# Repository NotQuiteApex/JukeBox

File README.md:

# 

An affordable, adorable, powerful hotkey device to run macros, play funny sounds, mute your microphone, change paint brush settings, or manage items in OBS! It can even have RGB or show PC stats!

(TODO: image here)

# Disclaimer
While this project is public, it is not ready for any sort of prime time.

# Docs and Assets
If you are the proud owner of a new JukeBox, or are building your own, take a look at the [getting started doc](docs/getting-started.md).

Sadly, not every program is compatible with these additional function keys, and some do not allow the use of these keys. There is a running list [here](docs/program-compatibility.md) of what programs do and do not work with the keys provided by JukeBox.

# Nightly builds
Each component of the project is built as it is updated. You can grab the latest version of each below. Nightly links provided by [nightly.link](https://nightly.link/).

| [Software, Windows (N/A)](https://nightly.link/FriendTeamInc/JukeBox/workflows/build-software.yaml/main/jb-software-windows.zip) | [Software, Linux](https://nightly.link/FriendTeamInc/JukeBox/workflows/build-software.yaml/main/jb-software-linux.zip) | [Firmware](https://nightly.link/FriendTeamInc/JukeBox/workflows/build-firmware.yaml/main/jb-firmware.zip) | [Hardware, Case](https://nightly.link/FriendTeamInc/JukeBox/workflows/build-hardware-case.yaml/main/jb-hardware-case.zip) | [Hardware, PCB](https://nightly.link/FriendTeamInc/JukeBox/workflows/build-hardware-pcb.yaml/main/jb-hardware-pcb.zip) |
| - | - | - | - | - |

# License
Copyright (c) 2020-2025 Logan "NotQuiteApex" Hickok-Dickson

All programming files, found in [`firmware/`](firmware/), [`software/`](software/), and [`hardware-case/`](hardware-case), are licensed under the [MIT license](https://mit-license.org/). All CAD files, found in [`hardware-pcb/`](hardware-pcb/), unless otherwise provided by an external source such as footprints or 3D models, are licesned under the [CC BY-NC-SA license](https://creativecommons.org/licenses/by-nc-sa/4.0/). Both licenses can be found with the given links or as files in the root of this repostiory.

If you would like to sell a variation of the board designed by you, reach out and an alternative license can be discussed and granted.

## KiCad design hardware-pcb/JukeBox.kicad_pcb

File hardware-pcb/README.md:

# JukeBox PCB
Made with KiCad 8, the PCB is the physical heart of the project.

Footprints and models:
- [Cherry/Kailh Switch footprint based on this.](https://github.com/luke-schutt/Pi5Keyboard/blob/main/Pi5-pcb/Pi5Footprints.pretty/Low%20Profile%20GC%20plus%20MX.kicad_mod)

Estimated power usage is 5 volts at 0.1 amps, or 0.5 watts.

## Bill of Materials
| Ref         | Part No.           | Qty | Value |
|-------------|--------------------|-----|-------|
| R1, R5, R14 | RMCF0402FT1K00     | 3   | 1k    |
| R3, R4      | RMCF0402FT27R0     | 2   | 27    |
| R6, R7      | RMCF0402FT5K11     | 2   | 5.11k |
| R8-12, R15  | RMCF0402FT10K0     | 5   | 10k   |
| R13         | RMCF0402FT10R0     | 1   | 10    |
| C1, C4      | GRM21BR61C106KE15K | 2   | 10u   |
| C2, C3      | GCM1555C1H150JA16D | 2   | 15p   |
| C5          | GRM155R71E104KE14J | 1   | 100n  |
| C8, C10     | GRM155C81A105KA12D | 2   | 1u    |
| D1-12       | 1N4148W-SOD-123    | 12  |       |
| D13-24      | WS2812B-2020       | 12  |       |
| D25         | 150080GS75000      | 1   |       |
| J1          | USB4105-GF-A       | 1   |       |
| Q1          | S8050-SOT-23       | 1   |       |
| U1          | AZ1117IH-3.3TRG1   | 1   |       |
| U2          | W25Q128JVSIQ-TR    | 1   |       |
| U3          | RP2040             | 1   |       |
| U4          | TFTQ-T20SH12ZP01   | 1   |       |
| U5          | CAT24C512          | 1   |       |
| Y1          | ABM8-272-T3        | 1   |       |

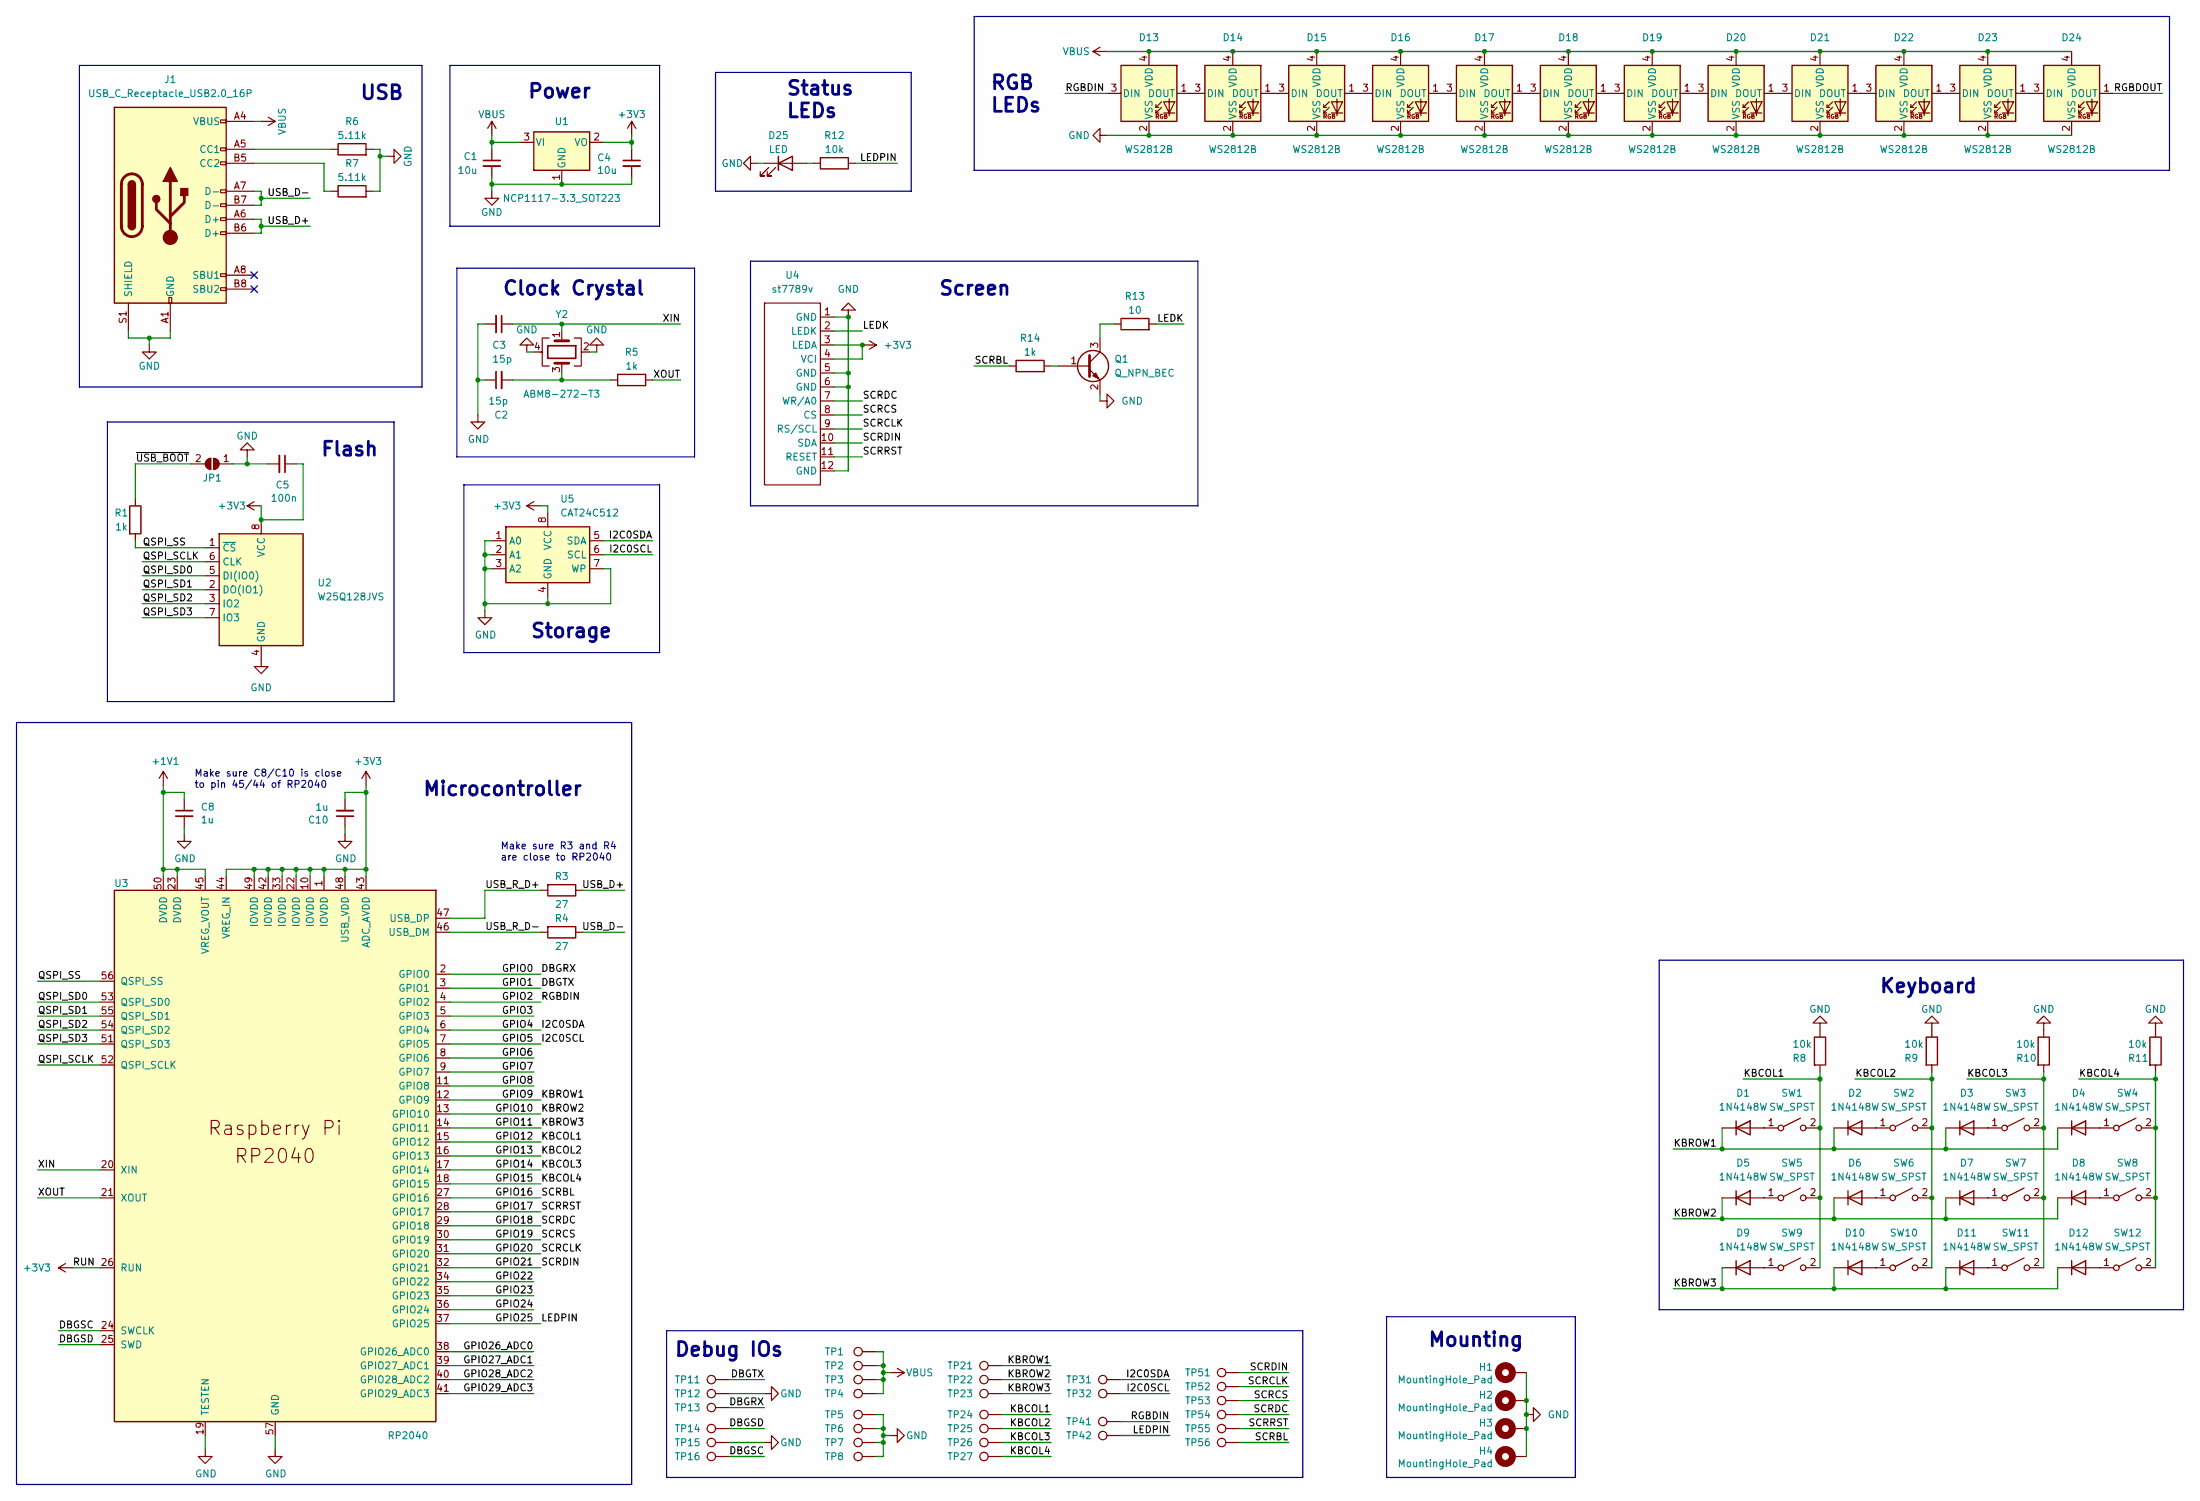
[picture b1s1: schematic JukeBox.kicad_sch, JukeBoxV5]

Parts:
C1, C4: 10u; C_0805_2012Metric
C2, C3: 15p; C_0402_1005Metric
C5: 100n; C_0402_1005Metric
C8, C10: 1u; C_0402_1005Metric
D1, D2, D3, D4, D5, D6, D7, D8, D9, D10, D11, D12: 1N4148W; D_SOD-123
D13, D14, D15, D16, D17, D18, D19, D20, D21, D22, D23, D24: WS2812B; LED_WS2812B-2020_PLCC4_2.0x2.0mm
D25: LED; D_0805_2012Metric_Pad1.15x1.40mm_HandSolder
H1, H2, H3, H4: MountingHole_Pad; MountingHole_3.2mm_M3_Pad_Via
J1: USB_C_Receptacle_USB2.0_16P; USB_C_Receptacle_GCT_USB4105-xx-A_16P_TopMnt_Horizontal
JP1: SolderJumper_2_Open; SolderJumper-2_P1.3mm_Open_RoundedPad1.0x1.5mm
Q1: Q_NPN_BEC; SOT-23
R1, R5, R14: 1k; R_0402_1005Metric
R3, R4: 27; R_0402_1005Metric
R6, R7: 5.11k; R_0402_1005Metric
R8, R9, R10, R11, R12: 10k; R_0402_1005Metric
R13: 10; R_0402_1005Metric
SW1, SW2, SW3, SW4, SW5, SW6, SW7, SW8, SW9, SW10, SW11, SW12: SW_SPST; ALLKEY
TP1, TP2, TP3, TP4, TP5, TP6, TP7, TP8, TP11, TP12, TP13, TP14, TP15, TP16, TP21, TP22, TP23, TP24, TP25, TP26, TP27, TP31, TP32, TP41, TP42, TP51, TP52, TP53, TP54, TP55, TP56: TestPoint; TestPoint_Pad_D1.5mm
U1: NCP1117-3.3_SOT223; SOT-223-3_TabPin2
U2: W25Q128JVS; SOIC-8_5.23x5.23mm_P1.27mm
U3: RP2040; RP2040-QFN-56
U4: st7789v
U5: CAT24C512; SOIC-8_3.9x4.9mm_P1.27mm
Y2: ABM8-272-T3; Crystal_SMD_Abracon_ABM8G-4Pin_3.2x2.5mm

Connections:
+1V1: C8.1, U3.23 (DVDD), U3.45 (VREG_VOUT), U3.50 (DVDD)
+3V3: C4.1, C5.1, C10.2, U1.2 (VO), U2.8 (VCC), U3.1 (IOVDD), U3.10 (IOVDD), U3.22 (IOVDD), U3.26 (RUN), U3.33 (IOVDD), U3.42 (IOVDD), U3.43 (ADC_AVDD), U3.44 (VREG_IN), U3.48 (USB_VDD), U3.49 (IOVDD), U4.3 (LEDA), U4.4 (VCI), U5.8 (VCC); also elsewhere on the board
/DBGRX: TP13.1, U3.2 (GPIO0)
/DBGSC: TP16.1, U3.24 (SWCLK)
/DBGSD: TP14.1, U3.25 (SWD)
/DBGTX: TP11.1, U3.3 (GPIO1)
/GPIO2: D13.3 (DIN), TP41.1, U3.4 (GPIO2)
/GPIO3: U3.5 (GPIO3)
/GPIO4: TP31.1, U3.6 (GPIO4), U5.5 (SDA)
/GPIO5: TP32.1, U3.7 (GPIO5), U5.6 (SCL)
/GPIO6: U3.8 (GPIO6)
/GPIO7: U3.9 (GPIO7)
/GPIO8: U3.11 (GPIO8)
/GPIO9: D1.2 (K), D2.2 (K), D3.2 (K), D4.2 (K), TP21.1, U3.12 (GPIO9)
/GPIO10: D5.2 (K), D6.2 (K), D7.2 (K), D8.2 (K), TP22.1, U3.13 (GPIO10)
/GPIO11: D9.2 (K), D10.2 (K), D11.2 (K), D12.2 (K), TP23.1, U3.14 (GPIO11)
/GPIO12: R8.2, SW1.2 (B), SW5.2 (B), SW9.2 (B), TP24.1, U3.15 (GPIO12)
/GPIO13: R9.2, SW2.2 (B), SW6.2 (B), SW10.2 (B), TP25.1, U3.16 (GPIO13)
/GPIO14: R10.2, SW3.2 (B), SW7.2 (B), SW11.2 (B), TP26.1, U3.17 (GPIO14)
/GPIO15: R11.2, SW4.2 (B), SW8.2 (B), SW12.2 (B), TP27.1, U3.18 (GPIO15)
/GPIO16: R14.1, TP56.1, U3.27 (GPIO16)
/GPIO17: TP55.1, U3.28 (GPIO17), U4.11 (RESET)
/GPIO18: TP54.1, U3.29 (GPIO18), U4.7 (WR/A0)
/GPIO19: TP53.1, U3.30 (GPIO19), U4.8 (CS)
/GPIO20: TP52.1, U3.31 (GPIO20), U4.9 (RS/SCL)
/GPIO21: TP51.1, U3.32 (GPIO21), U4.10 (SDA)
/GPIO22: U3.34 (GPIO22)
/GPIO23: U3.35 (GPIO23)
/GPIO24: U3.36 (GPIO24)
/GPIO25: R12.1, TP42.1, U3.37 (GPIO25)
/GPIO26_ADC0: U3.38 (GPIO26_ADC0)
/GPIO27_ADC1: U3.39 (GPIO27_ADC1)
/GPIO28_ADC2: U3.40 (GPIO28_ADC2)
/GPIO29_ADC3: U3.41 (GPIO29_ADC3)
/LEDK: R13.2, U4.2 (LEDK)
/QSPI_SCLK: U2.6 (CLK), U3.52 (QSPI_SCLK)
/QSPI_SD0: U2.5 (DI(IO0)), U3.53 (QSPI_SD0)
/QSPI_SD1: U2.2 (DO(IO1)), U3.55 (QSPI_SD1)
/QSPI_SD2: U2.3 (IO2), U3.54 (QSPI_SD2)
/QSPI_SD3: U2.7 (IO3), U3.51 (QSPI_SD3)
/QSPI_SS: R1.2, U2.1 (~CS), U3.56 (QSPI_SS)
/RGBDOUT: D24.1 (DOUT)
/USB_D+: J1.A6 (D+), J1.B6 (D+), R3.1
/USB_D-: J1.A7 (D-), J1.B7 (D-), R4.1
/USB_R_D+: R3.2, U3.47 (USB_DP)
/USB_R_D-: R4.2, U3.46 (USB_DM)
/XIN: C3.1, U3.20 (XIN), Y2.1
/XOUT: R5.1, U3.21 (XOUT)
/~USB_BOOT: JP1.2 (B), R1.1
GND: C1.2, C2.1, C3.2, C4.2, C5.2, C8.2, C10.1, D13.2 (VSS), D14.2 (VSS), D15.2 (VSS), D16.2 (VSS), D17.2 (VSS), D18.2 (VSS), D19.2 (VSS), D20.2 (VSS), D21.2 (VSS), D22.2 (VSS), D23.2 (VSS), D24.2 (VSS), D25.1 (K), H1.1, H2.1, H3.1, H4.1, J1.A1 (GND), J1.A12 (GND), J1.B1 (GND), J1.B12 (GND), J1.S1 (SHIELD), JP1.1 (A), Q1.2 (E), R6.2, R7.2, R8.1, R9.1, R10.1, R11.1, TP5.1, TP6.1, TP7.1, TP8.1, TP12.1, TP15.1, U1.1 (GND), U2.4 (GND), U3.19 (TESTEN), U3.57 (GND), U4.1 (GND), U4.5 (GND), U4.6 (GND), U4.12 (GND), U5.1 (A0), U5.2 (A1), U5.3 (A2), U5.4 (GND), U5.7 (WP), Y2.2, Y2.4
unnamed: C2.2, R5.2, Y2.3
unnamed: D1.1 (A), SW1.1 (A)
unnamed: D2.1 (A), SW2.1 (A)
unnamed: D3.1 (A), SW3.1 (A)
unnamed: D4.1 (A), SW4.1 (A)
unnamed: D5.1 (A), SW5.1 (A)
unnamed: D6.1 (A), SW6.1 (A)
unnamed: D7.1 (A), SW7.1 (A)
unnamed: D8.1 (A), SW8.1 (A)
unnamed: D9.1 (A), SW9.1 (A)
unnamed: D10.1 (A), SW10.1 (A)
unnamed: D11.1 (A), SW11.1 (A)
unnamed: D12.1 (A), SW12.1 (A)
unnamed: D13.1 (DOUT), D14.3 (DIN)
unnamed: D14.1 (DOUT), D15.3 (DIN)
unnamed: D15.1 (DOUT), D16.3 (DIN)
unnamed: D16.1 (DOUT), D17.3 (DIN)
unnamed: D17.1 (DOUT), D18.3 (DIN)
unnamed: D18.1 (DOUT), D19.3 (DIN)
unnamed: D19.1 (DOUT), D20.3 (DIN)
unnamed: D20.1 (DOUT), D21.3 (DIN)
unnamed: D21.1 (DOUT), D22.3 (DIN)
unnamed: D22.1 (DOUT), D23.3 (DIN)
unnamed: D23.1 (DOUT), D24.3 (DIN)
unnamed: D25.2 (A), R12.2
unnamed: J1.A5 (CC1), R6.1
unnamed: J1.B5 (CC2), R7.1
unnamed 77: Q1.1 (B), R14.2; also elsewhere on the board
unnamed: Q1.3 (C), R13.1
VBUS: C1.1, D13.4 (VDD), D14.4 (VDD), D15.4 (VDD), D16.4 (VDD), D17.4 (VDD), D18.4 (VDD), D19.4 (VDD), D20.4 (VDD), D21.4 (VDD), D22.4 (VDD), D23.4 (VDD), D24.4 (VDD), J1.A4 (VBUS), J1.A9 (VBUS), J1.B4 (VBUS), J1.B9 (VBUS), TP1.1, TP2.1, TP3.1, TP4.1, U1.3 (VI)

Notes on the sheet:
Flash
Make sure C8/C10 is close to pin 45/44 of RP2040
Mounting
Debug IOs
Storage
Keyboard
USB
Make sure R3 and R4 are close to RP2040
RGB LEDs
Screen
Power
Clock Crystal
Microcontroller
Status LEDs

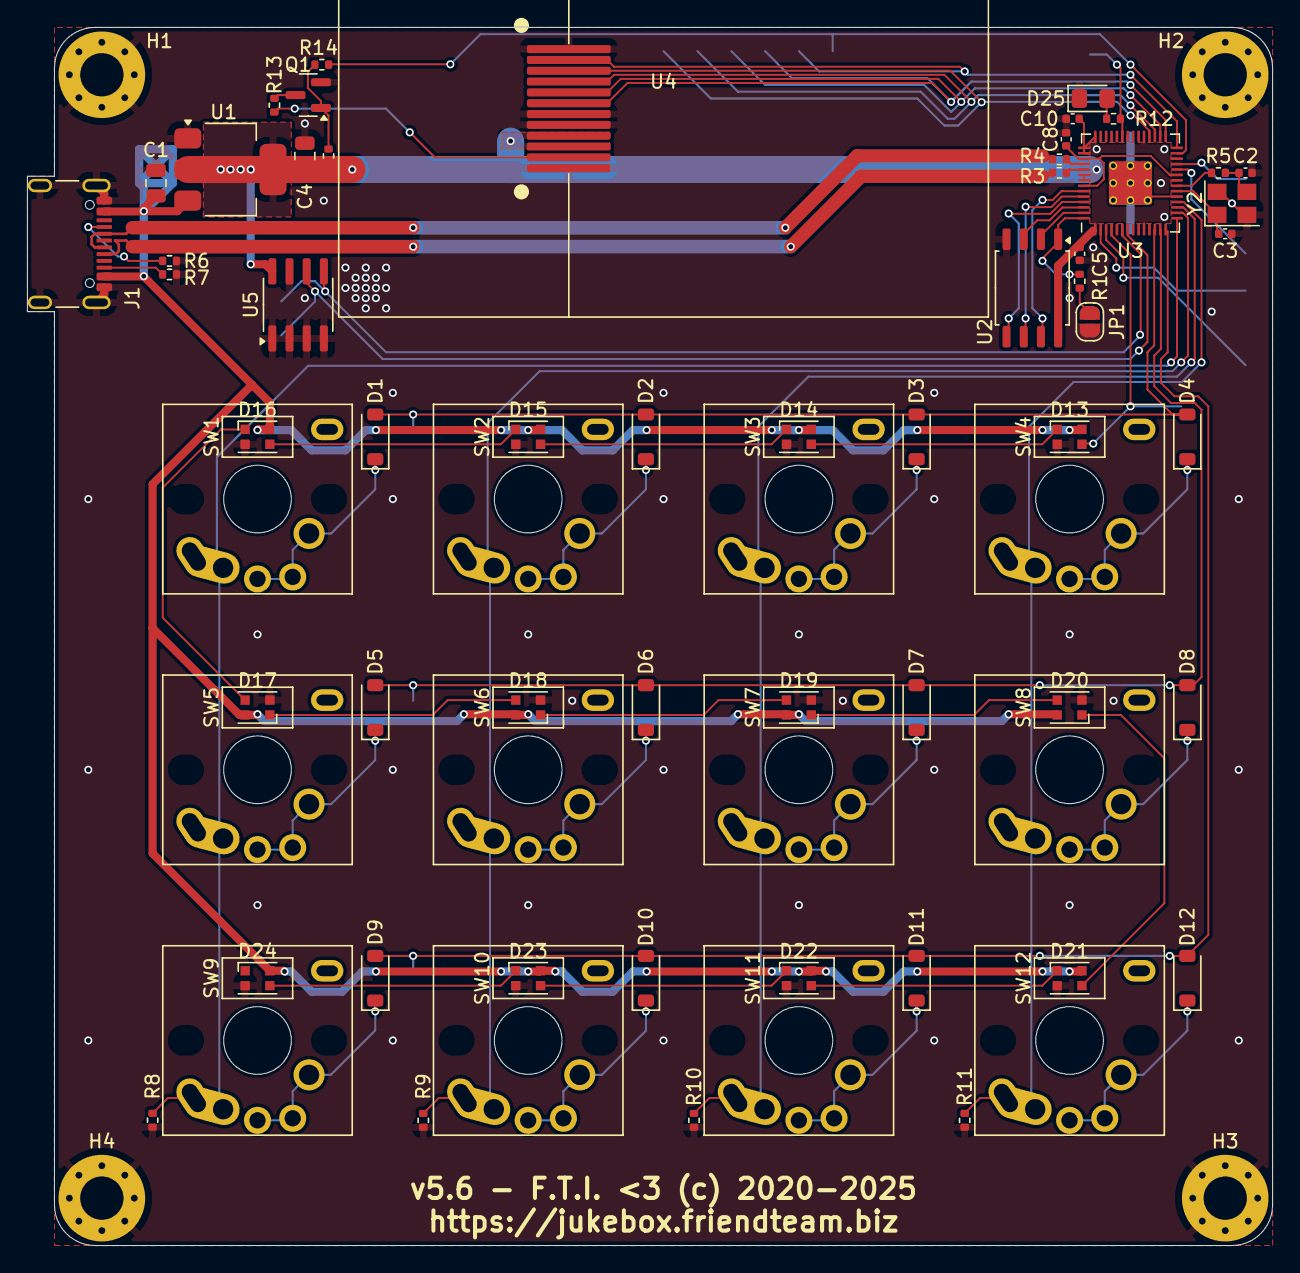
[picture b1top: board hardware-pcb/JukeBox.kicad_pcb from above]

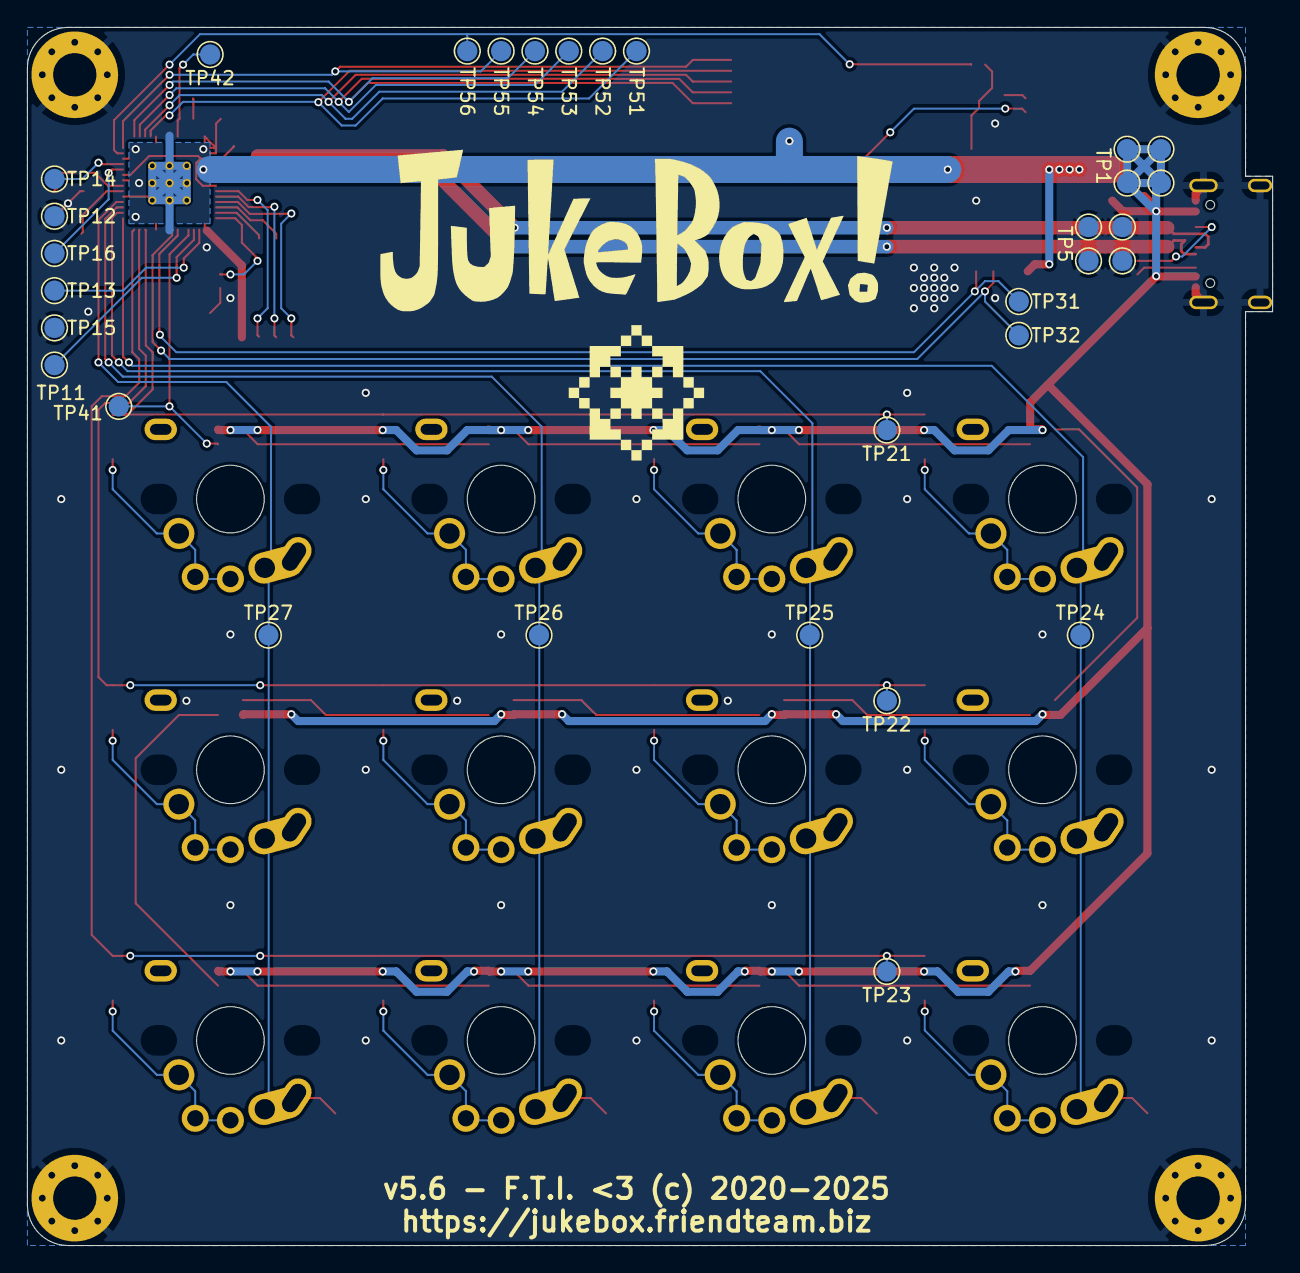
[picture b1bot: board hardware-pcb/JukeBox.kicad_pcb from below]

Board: 2 copper layers, 92.0 x 90.0 mm, 103 parts (32 on the bottom side), 68 nets.

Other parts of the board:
G1: LOGO; JukeBox
R15: 10k; R_0402_1005Metric

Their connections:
+3V3: R15.1; also elsewhere on the board
unnamed 77: R15.2; also elsewhere on the board

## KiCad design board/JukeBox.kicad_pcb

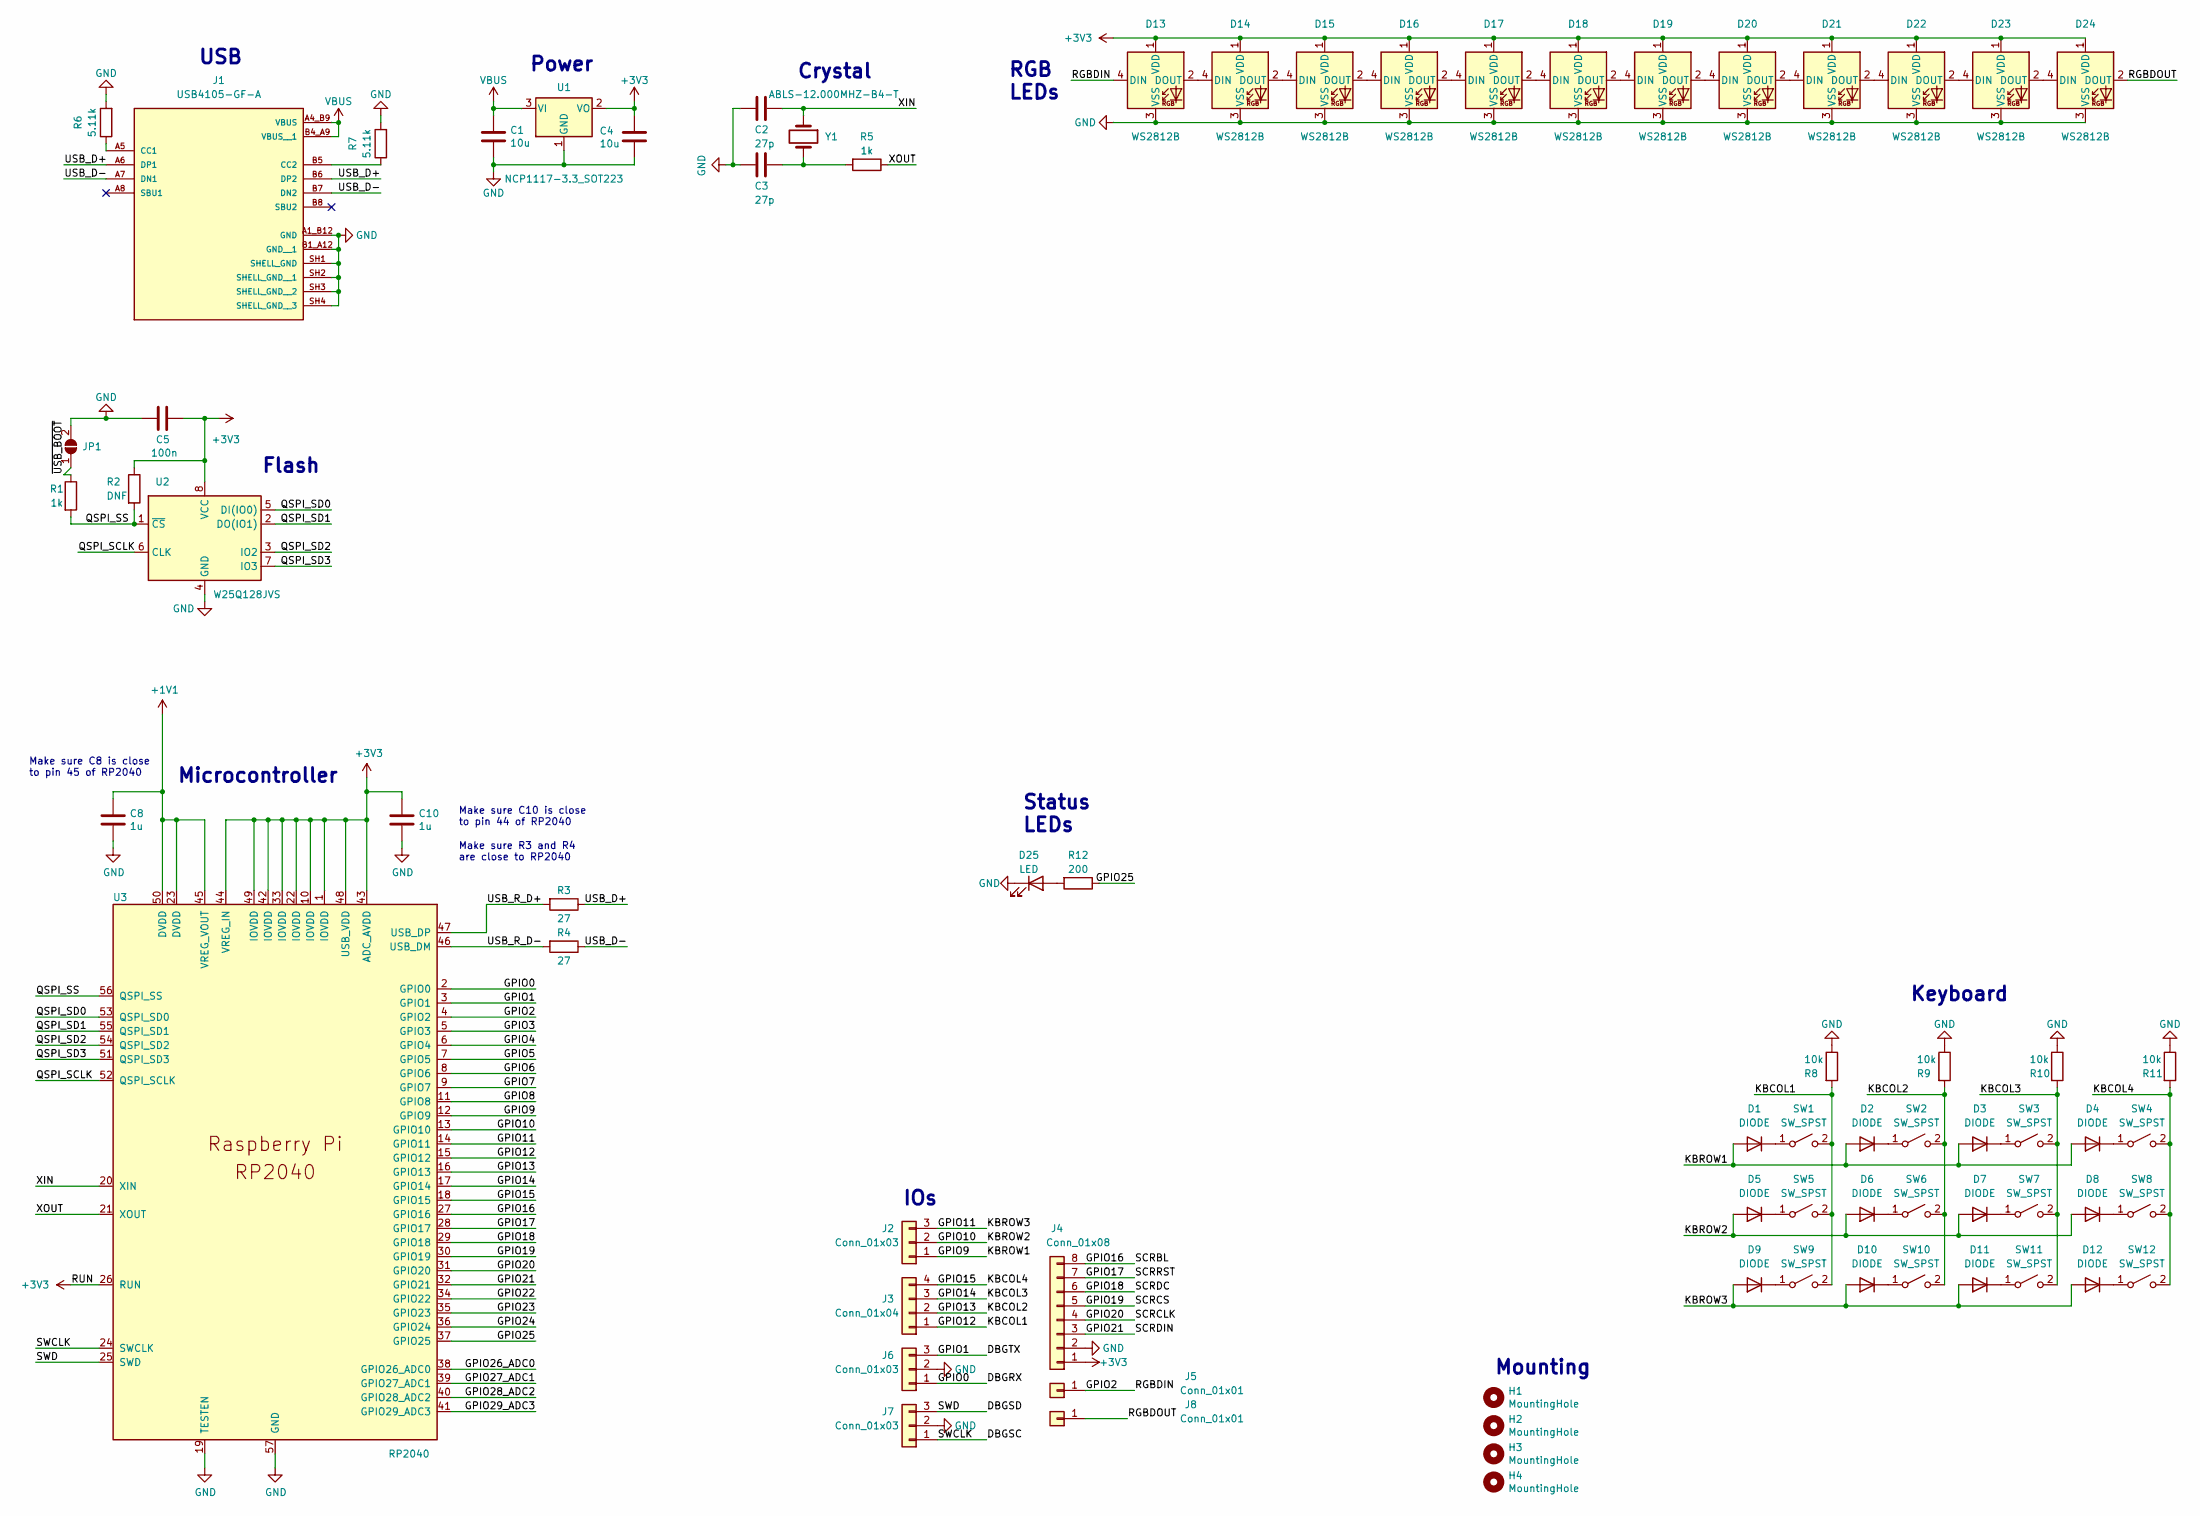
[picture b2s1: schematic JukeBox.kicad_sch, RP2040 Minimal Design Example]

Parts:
C1, C4: 10u; C_1206_3216Metric_Pad1.33x1.80mm_HandSolder
C2, C3: 27p; C_1206_3216Metric_Pad1.33x1.80mm_HandSolder
C5: 100n; C_1206_3216Metric_Pad1.33x1.80mm_HandSolder
C8, C10: 1u; C_1206_3216Metric_Pad1.33x1.80mm_HandSolder
D1, D2, D3, D4, D5, D6, D7, D8, D9, D10, D11, D12: DIODE; D_1206_3216Metric_Pad1.42x1.75mm_HandSolder
D13, D14, D15, D16, D17, D18, D19, D20, D21, D22, D23, D24: WS2812B; LED_WS2812B_PLCC4_5.0x5.0mm_P3.2mm
D25: LED; D_1206_3216Metric_Pad1.42x1.75mm_HandSolder
H1, H2, H3, H4: MountingHole; MountingHole_2.7mm_M2.5
J1: USB4105-GF-A; GCT_USB4105-GF-A; PARTREV B3
J2, J6, J7: Conn_01x03; PinHeader_1x03_P2.54mm_Vertical
J3: Conn_01x04; PinHeader_1x04_P2.54mm_Vertical
J4: Conn_01x08; PinHeader_1x08_P2.54mm_Vertical
J5, J8: Conn_01x01; PinHeader_1x01_P2.54mm_Vertical
JP1: SolderJumper_2_Open; SolderJumper-2_P1.3mm_Open_RoundedPad1.0x1.5mm
R1, R5: 1k; R_1206_3216Metric_Pad1.30x1.75mm_HandSolder
R2: DNF; R_1206_3216Metric_Pad1.30x1.75mm_HandSolder
R3, R4: 27; R_1206_3216Metric_Pad1.30x1.75mm_HandSolder
R6, R7: 5.11k; R_1206_3216Metric_Pad1.30x1.75mm_HandSolder
R8, R9, R10, R11: 10k; R_1206_3216Metric_Pad1.30x1.75mm_HandSolder
R12: 200; R_1206_3216Metric_Pad1.30x1.75mm_HandSolder
SW1, SW2, SW3, SW4, SW5, SW6, SW7, SW8, SW9, SW10, SW11, SW12: SW_SPST; Kailh_Choc_MX_Key
U1: NCP1117-3.3_SOT223; SOT-223-3_TabPin2
U2: W25Q128JVS; SOIC-8_5.23x5.23mm_P1.27mm
U3: RP2040; RP2040-QFN-56
Y1: ABLS-12.000MHZ-B4-T; Crystal_SMD_HC49-US

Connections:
+1V1: C8.1, U3.23 (DVDD), U3.45 (VREG_VOUT), U3.50 (DVDD)
+3V3: C4.1, C5.1, C10.1, D13.1 (VDD), D14.1 (VDD), D15.1 (VDD), D16.1 (VDD), D17.1 (VDD), D18.1 (VDD), D19.1 (VDD), D20.1 (VDD), D21.1 (VDD), D22.1 (VDD), D23.1 (VDD), D24.1 (VDD), J4.1, R2.1, U1.2 (VO), U2.8 (VCC), U3.1 (IOVDD), U3.10 (IOVDD), U3.22 (IOVDD), U3.26 (RUN), U3.33 (IOVDD), U3.42 (IOVDD), U3.43 (ADC_AVDD), U3.44 (VREG_IN), U3.48 (USB_VDD), U3.49 (IOVDD)
/DBGRX: J6.1, U3.2 (GPIO0)
/DBGSC: J7.1, U3.24 (SWCLK)
/DBGSD: J7.3, U3.25 (SWD)
/DBGTX: J6.3, U3.3 (GPIO1)
/GPIO2: D13.4 (DIN), J5.1, U3.4 (GPIO2)
/GPIO3: U3.5 (GPIO3)
/GPIO4: U3.6 (GPIO4)
/GPIO5: U3.7 (GPIO5)
/GPIO6: U3.8 (GPIO6)
/GPIO7: U3.9 (GPIO7)
/GPIO8: U3.11 (GPIO8)
/GPIO9: D1.1 (A), D2.1 (A), D3.1 (A), D4.1 (A), J2.1, U3.12 (GPIO9)
/GPIO10: D5.1 (A), D6.1 (A), D7.1 (A), D8.1 (A), J2.2, U3.13 (GPIO10)
/GPIO11: D9.1 (A), D10.1 (A), D11.1 (A), D12.1 (A), J2.3, U3.14 (GPIO11)
/GPIO12: J3.1, R8.2, SW1.2 (B), SW5.2 (B), SW9.2 (B), U3.15 (GPIO12)
/GPIO13: J3.2, R9.2, SW2.2 (B), SW6.2 (B), SW10.2 (B), U3.16 (GPIO13)
/GPIO14: J3.3, R10.2, SW3.2 (B), SW7.2 (B), SW11.2 (B), U3.17 (GPIO14)
/GPIO15: J3.4, R11.2, SW4.2 (B), SW8.2 (B), SW12.2 (B), U3.18 (GPIO15)
/GPIO16: J4.8, U3.27 (GPIO16)
/GPIO17: J4.7, U3.28 (GPIO17)
/GPIO18: J4.6, U3.29 (GPIO18)
/GPIO19: J4.5, U3.30 (GPIO19)
/GPIO20: J4.4, U3.31 (GPIO20)
/GPIO21: J4.3, U3.32 (GPIO21)
/GPIO22: U3.34 (GPIO22)
/GPIO23: U3.35 (GPIO23)
/GPIO24: U3.36 (GPIO24)
/GPIO25: R12.1, U3.37 (GPIO25)
/GPIO26_ADC0: U3.38 (GPIO26_ADC0)
/GPIO27_ADC1: U3.39 (GPIO27_ADC1)
/GPIO28_ADC2: U3.40 (GPIO28_ADC2)
/GPIO29_ADC3: U3.41 (GPIO29_ADC3)
/QSPI_SCLK: U2.6 (CLK), U3.52 (QSPI_SCLK)
/QSPI_SD0: U2.5 (DI(IO0)), U3.53 (QSPI_SD0)
/QSPI_SD1: U2.2 (DO(IO1)), U3.55 (QSPI_SD1)
/QSPI_SD2: U2.3 (IO2), U3.54 (QSPI_SD2)
/QSPI_SD3: U2.7 (IO3), U3.51 (QSPI_SD3)
/QSPI_SS: R1.2, R2.2, U2.1 (~CS), U3.56 (QSPI_SS)
/RGBDOUT: D24.2 (DOUT), J8.1
/USB_D+: J1.A6 (DP1), J1.B6 (DP2), R3.1
/USB_D-: J1.A7 (DN1), J1.B7 (DN2), R4.1
/USB_R_D+: R3.2, U3.47 (USB_DP)
/USB_R_D-: R4.2, U3.46 (USB_DM)
/XIN: C2.1, U3.20 (XIN), Y1.1
/XOUT: R5.1, U3.21 (XOUT)
/~USB_BOOT: JP1.1 (A), R1.1
GND: C1.2, C2.2, C3.2, C4.2, C5.2, C8.2, C10.2, D13.3 (VSS), D14.3 (VSS), D15.3 (VSS), D16.3 (VSS), D17.3 (VSS), D18.3 (VSS), D19.3 (VSS), D20.3 (VSS), D21.3 (VSS), D22.3 (VSS), D23.3 (VSS), D24.3 (VSS), D25.1 (K), J1.A1_B12 (GND), J1.B1_A12 (GND__1), J1.SH1 (SHELL_GND), J1.SH2 (SHELL_GND__1), J1.SH3 (SHELL_GND__2), J1.SH4 (SHELL_GND__3), J4.2, J6.2, J7.2, JP1.2 (B), R6.2, R7.2, R8.1, R9.1, R10.1, R11.1, U1.1 (GND), U2.4 (GND), U3.19 (TESTEN), U3.57 (GND)
unnamed: C3.1, R5.2, Y1.2
unnamed: D1.2 (K), SW1.1 (A)
unnamed: D2.2 (K), SW2.1 (A)
unnamed: D3.2 (K), SW3.1 (A)
unnamed: D4.2 (K), SW4.1 (A)
unnamed: D5.2 (K), SW5.1 (A)
unnamed: D6.2 (K), SW6.1 (A)
unnamed: D7.2 (K), SW7.1 (A)
unnamed: D8.2 (K), SW8.1 (A)
unnamed: D9.2 (K), SW9.1 (A)
unnamed: D10.2 (K), SW10.1 (A)
unnamed: D11.2 (K), SW11.1 (A)
unnamed: D12.2 (K), SW12.1 (A)
unnamed: D13.2 (DOUT), D14.4 (DIN)
unnamed: D14.2 (DOUT), D15.4 (DIN)
unnamed: D15.2 (DOUT), D16.4 (DIN)
unnamed: D16.2 (DOUT), D17.4 (DIN)
unnamed: D17.2 (DOUT), D18.4 (DIN)
unnamed: D18.2 (DOUT), D19.4 (DIN)
unnamed: D19.2 (DOUT), D20.4 (DIN)
unnamed: D20.2 (DOUT), D21.4 (DIN)
unnamed: D21.2 (DOUT), D22.4 (DIN)
unnamed: D22.2 (DOUT), D23.4 (DIN)
unnamed: D23.2 (DOUT), D24.4 (DIN)
unnamed: D25.2 (A), R12.2
unnamed: J1.A5 (CC1), R6.1
unnamed: J1.B5 (CC2), R7.1
VBUS: C1.1, J1.A4_B9 (VBUS), J1.B4_A9 (VBUS__1), U1.3 (VI)

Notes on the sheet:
Make sure C10 is close to pin 44 of RP2040
Make sure C8 is close to pin 45 of RP2040
Mounting
Flash
IOs
Keyboard
USB
Make sure R3 and R4 are close to RP2040
RGB LEDs
Power
Crystal
Microcontroller
Status LEDs

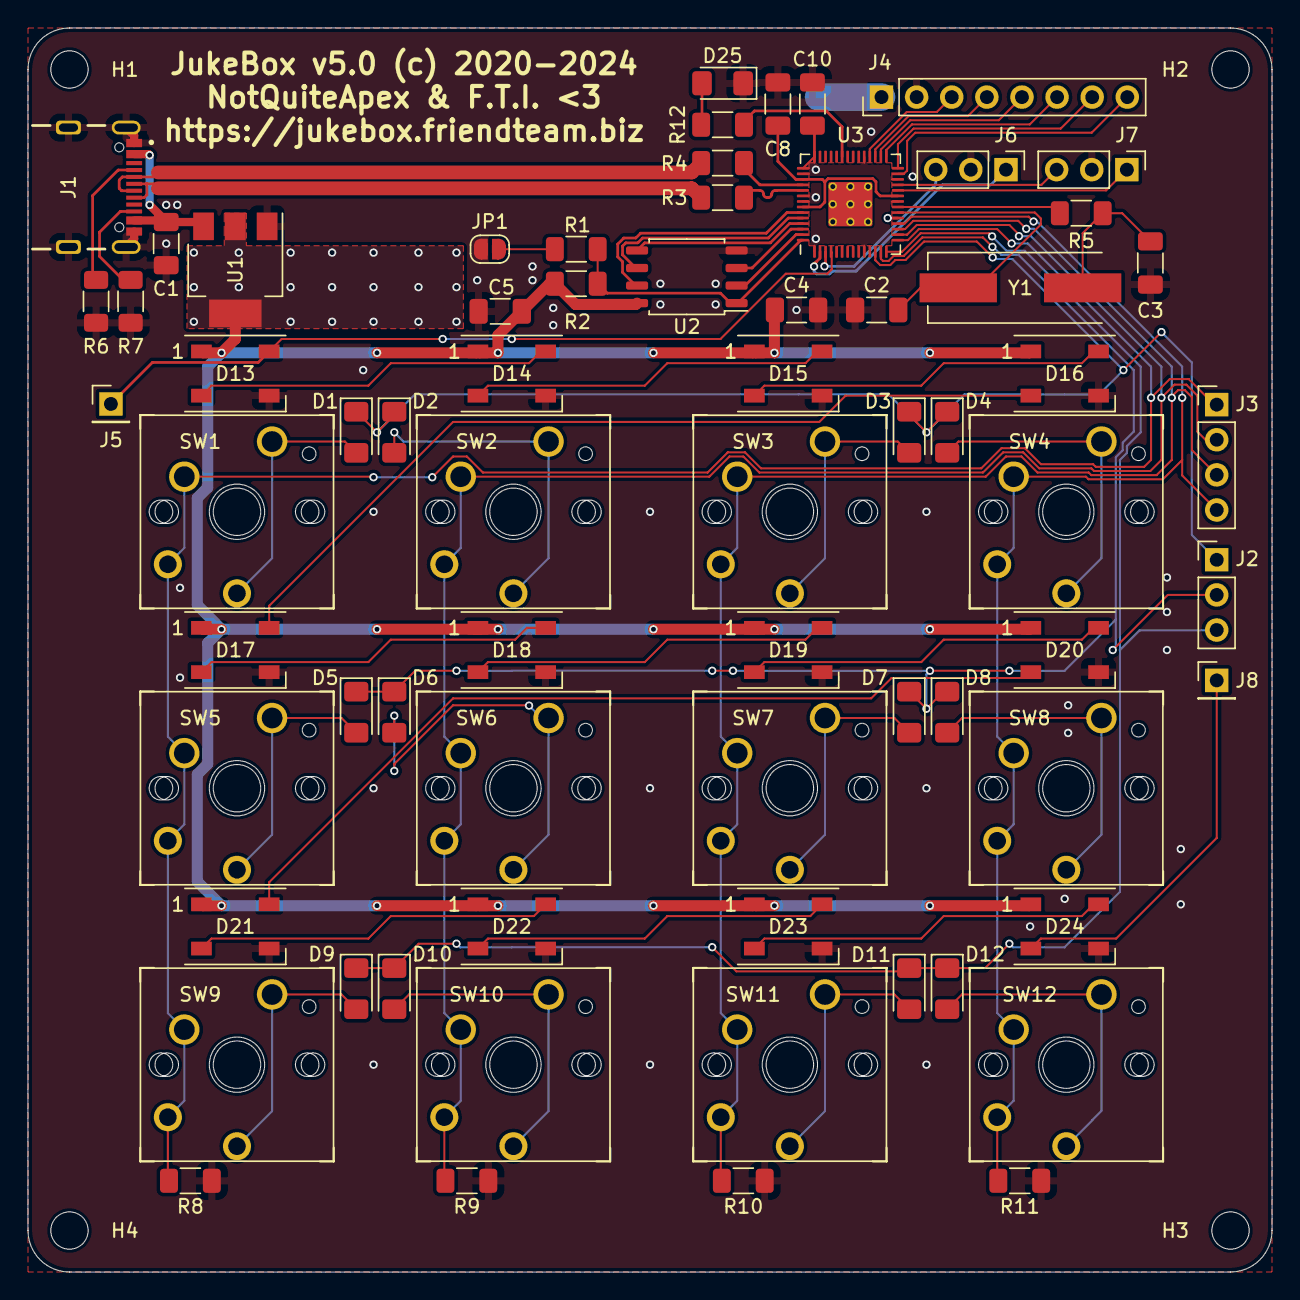
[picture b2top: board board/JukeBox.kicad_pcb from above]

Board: 2 copper layers, 90.0 x 90.0 mm, 73 parts (0 on the bottom side), 64 nets.

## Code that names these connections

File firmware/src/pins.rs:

use rp_pico::{
    hal::gpio::{
        DynPinId, FunctionPio0, FunctionPio1, FunctionSioInput, FunctionSioOutput, Pin, PullDown,
    },
    Pins,
};

use crate::keyboard::{KEY_COLS, KEY_ROWS};

pub fn configure_gpio(
    pins: Pins,
) -> (
    // keyboard keys
    [Pin<DynPinId, FunctionSioInput, PullDown>; KEY_COLS],
    [Pin<DynPinId, FunctionSioOutput, PullDown>; KEY_ROWS],
    // led pin
    Pin<DynPinId, FunctionSioOutput, PullDown>,
    // rgb pin
    Pin<DynPinId, FunctionPio0, PullDown>,
    // screen pins
    (
        Pin<DynPinId, FunctionPio1, PullDown>,      // data
        Pin<DynPinId, FunctionPio1, PullDown>,      // clock
        Pin<DynPinId, FunctionSioOutput, PullDown>, // cs
        Pin<DynPinId, FunctionSioOutput, PullDown>, // dc
        Pin<DynPinId, FunctionSioOutput, PullDown>, // rst
        Pin<DynPinId, FunctionSioOutput, PullDown>, // backlight
    ),
) {
    (
        // keyboard keys
        [
            pins.gpio12.into_function().into_dyn_pin().into_pull_type(),
            pins.gpio13.into_function().into_dyn_pin().into_pull_type(),
            pins.gpio14.into_function().into_dyn_pin().into_pull_type(),
            pins.gpio15.into_function().into_dyn_pin().into_pull_type(),
        ],
        [
            pins.gpio9.into_function().into_dyn_pin().into_pull_type(),
            pins.gpio10.into_function().into_dyn_pin().into_pull_type(),
            pins.gpio11.into_function().into_dyn_pin().into_pull_type(),
        ],
        // led pin
        pins.led.into_function().into_dyn_pin().into_pull_type(),
        // rgb pin
        pins.gpio2.into_function().into_dyn_pin().into_pull_type(),
        // screen pins
        (
            pins.gpio21.into_function().into_dyn_pin().into_pull_type(), // data
            pins.gpio20.into_function().into_dyn_pin().into_pull_type(), // clock
            pins.gpio19.into_function().into_dyn_pin().into_pull_type(), // cs
            pins.gpio18.into_function().into_dyn_pin().into_pull_type(), // dc
            pins.gpio17.into_function().into_dyn_pin().into_pull_type(), // rst
            pins.gpio16.into_function().into_dyn_pin().into_pull_type(), // backlight
        ),
    )
}

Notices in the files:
board/JukeBox.kicad_pcb:
JukeBox v5.0 (c) 2020-2024
hardware-pcb/JukeBox.kicad_pcb:
v5.6 - F.T.I. <3 (c) 2020-2025
